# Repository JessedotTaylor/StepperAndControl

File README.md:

These are the complete development and handin files from one of my 4th year projects. 

The assignment brief is provided in the 'Context' subdirectory.
The first pass code for the AT-Mega 32u4 is in the 'Microcontroller Code' subdirectory.
The first pass QT UI code is in the 'PC Control Code' subdirectory.
The PCB design files are in the 'PCB Files' subdirectory. They were designed in Ki-Cad.

The final report, written between me and another student, Josh Baynes, is listed as 'Stepper and Control Report Jesse Taylor Josh Baynes'

In summary, we were asked to design a full mechatronic system for a 1-D stepper motor linear actuator, and write microcontroller and PC support software.
The microcontroller code is dependent on third party libraries, linked below.

TMC2130Stepper Library:
[[https://github.com/teemuatlut/TMC2130Stepper](https://github.com/teemuatlut/TMC2130Stepper)]

AccelStepper Library:
[[https://www.airspayce.com/mikem/arduino/AccelStepper/](https://www.airspayce.com/mikem/arduino/AccelStepper/)]

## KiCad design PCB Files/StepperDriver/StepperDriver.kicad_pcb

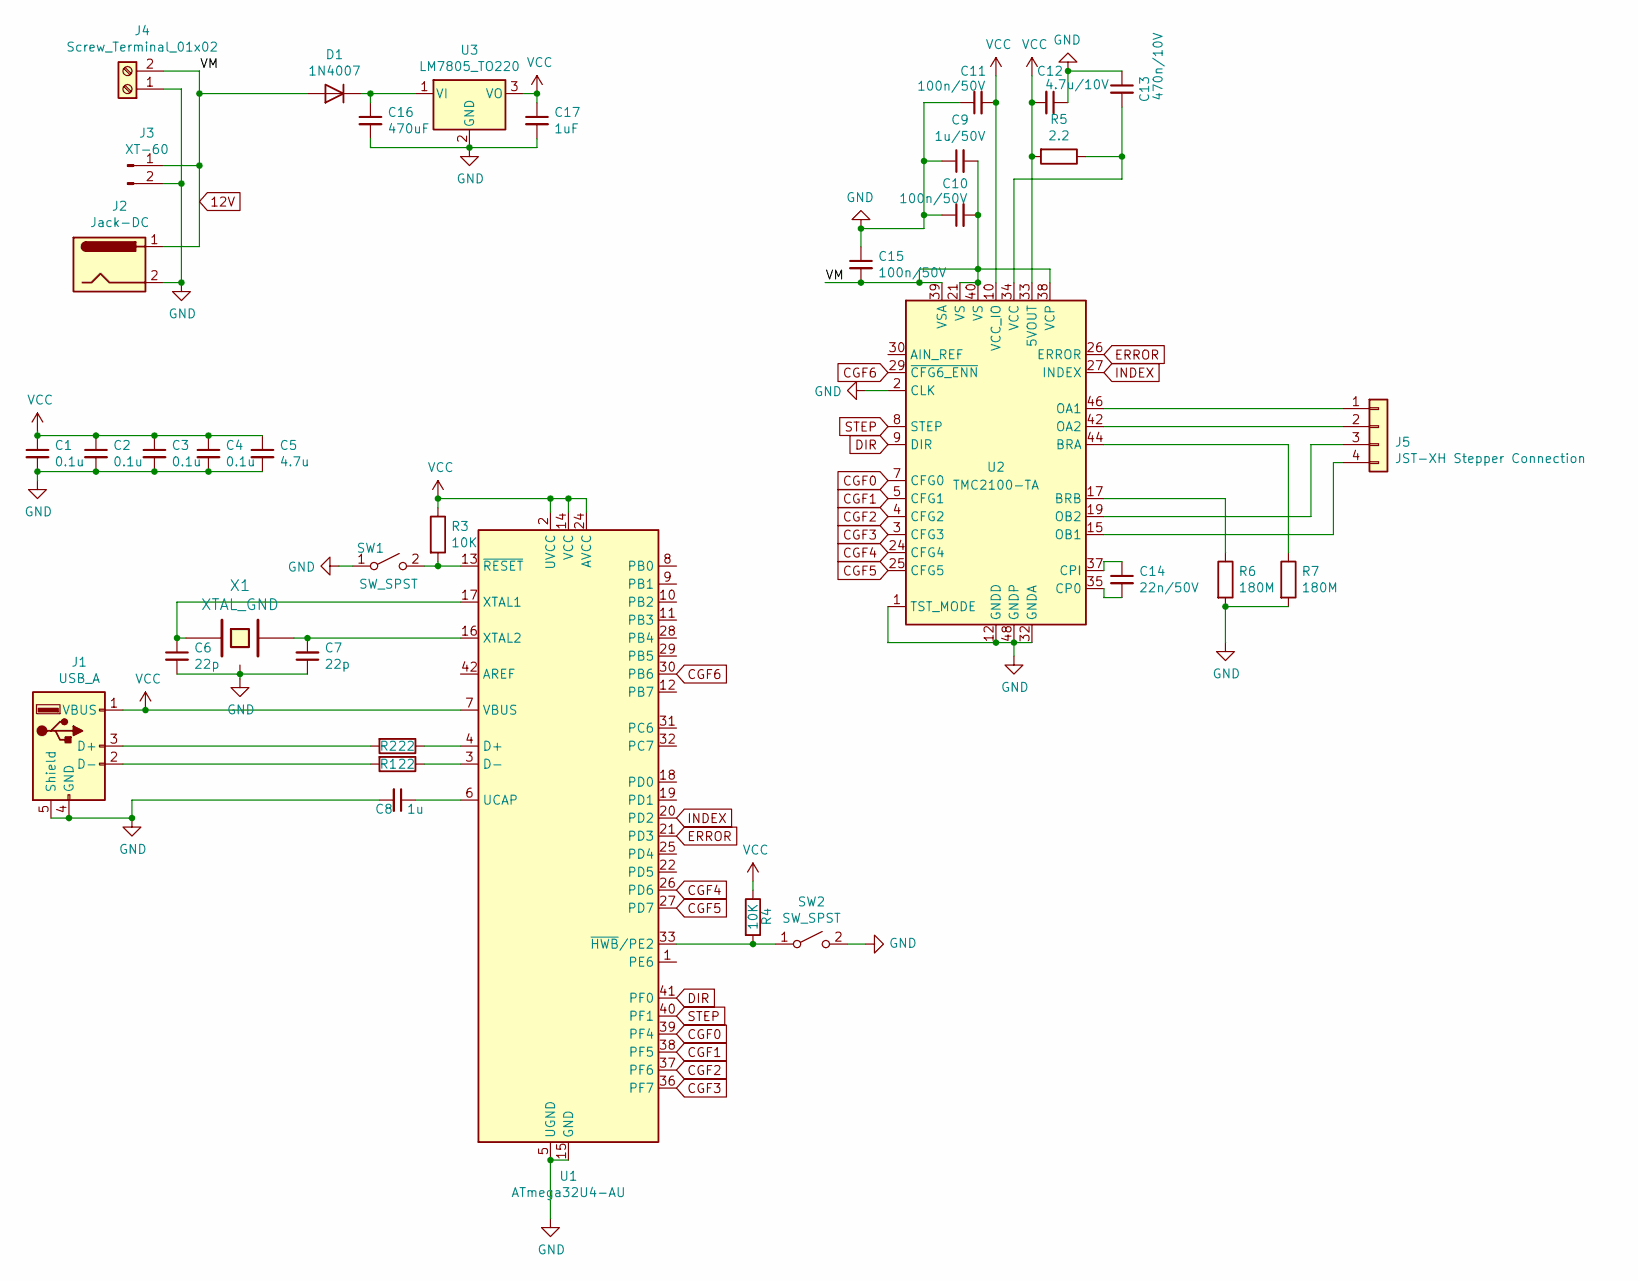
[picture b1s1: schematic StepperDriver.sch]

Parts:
C1, C2, C3, C4: 0.1u; C_0805_2012Metric_Pad1.15x1.40mm_HandSolder
C5: 4.7u; C_0805_2012Metric_Pad1.15x1.40mm_HandSolder
C6, C7: 22p; C_0805_2012Metric_Pad1.15x1.40mm_HandSolder
C8: 1u; C_0805_2012Metric_Pad1.15x1.40mm_HandSolder
C9: 1u/50V; C_0805_2012Metric_Pad1.15x1.40mm_HandSolder
C10, C11, C15: 100n/50V; C_2010_5025Metric_Pad1.52x2.65mm_HandSolder
C12: 4.7u/10V; C_0805_2012Metric_Pad1.15x1.40mm_HandSolder
C13: 470n/10V; C_0805_2012Metric_Pad1.15x1.40mm_HandSolder
C14: 22n/50V; C_2010_5025Metric_Pad1.52x2.65mm_HandSolder
C16: 470uF; CP_Radial_D4.0mm_P1.50mm
C17: 1uF; CP_Radial_D4.0mm_P1.50mm
D1: 1N4007; D_DO-41_SOD81_P10.16mm_Horizontal
J1: USB_A; USB_A_Molex_67643_Horizontal
J2: Jack-DC; BarrelJack_Horizontal
J3: XT-60; TestPoint_2Pads_Pitch5.08mm_Drill1.3mm
J4: Screw_Terminal_01x02; TerminalBlock_Altech_AK300-2_P5.00mm
J5: JST-XH Stepper Connection; JST_XH_B4B-XH-A_1x04_P2.50mm_Vertical
R1, R2: 22; R_0805_2012Metric_Pad1.15x1.40mm_HandSolder
R3, R4: 10K; R_0805_2012Metric_Pad1.15x1.40mm_HandSolder
R5: 2.2; R_0805_2012Metric_Pad1.15x1.40mm_HandSolder
R6, R7: 180M; R_0805_2012Metric_Pad1.15x1.40mm_HandSolder
SW1, SW2: SW_SPST; SW_SPST_TL3342
U1: ATmega32U4-AU; TQFP-44_10x10mm_P0.8mm
U2: TMC2100-TA; TQFP-48-1EP_7x7mm_P0.5mm_EP5x5mm_ThermalVias
U3: LM7805_TO220; TO-220-3_Vertical
X1: XTAL_GND; Crystal_SMD_SeikoEpson_FA238-4Pin_3.2x2.5mm_HandSoldering

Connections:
12V: C9.2, C10.2, C15.2, D1.2 (A), J2.1, J3.1, J4.2, U2.21 (VS), U2.38 (VCP), U2.39 (VSA), U2.40 (VS)
CGF0: U1.39 (PF4), U2.7 (CFG0)
CGF1: U1.38 (PF5), U2.5 (CFG1)
CGF2: U1.37 (PF6), U2.4 (CFG2)
CGF3: U1.36 (PF7), U2.3 (CFG3)
CGF4: U1.26 (PD6), U2.24 (CFG4)
CGF5: U1.27 (PD7), U2.25 (CFG5)
CGF6: U1.30 (PB6), U2.29 (~CFG6_ENN)
DIR: U1.41 (PF0), U2.9 (DIR)
ERROR: U1.21 (PD3), U2.26 (ERROR)
GND: C1.2, C2.2, C3.2, C4.2, C5.2, C6.2, C7.1, C8.2, C9.1, C10.1, C11.1, C12.1, C13.1, C15.1, C16.2, C17.2, J1.4 (GND), J1.5 (Shield), J2.2, J3.2, J4.1, R6.2, R7.2, SW1.1 (A), SW2.2 (B), U1.5 (UGND), U1.15 (GND), U1.23 (GND), U1.35 (GND), U1.43 (GND), U2.1 (TST_MODE), U2.2 (CLK), U2.6 (GNDD), U2.12 (GNDD), U2.13 (GNDP), U2.31 (GNDD), U2.32 (GNDA), U2.36 (GNDD), U2.48 (GNDP), U2.49 (GNDD), U3.2 (GND), X1.3
INDEX: U1.20 (PD2), U2.27 (INDEX)
unnamed: C6.1, U1.17 (XTAL1), X1.1
unnamed: C7.2, U1.16 (XTAL2), X1.2
unnamed: C8.1, U1.6 (UCAP)
unnamed: C13.2, R5.1, U2.34 (VCC)
unnamed: C14.1, U2.37 (CPI)
unnamed: C14.2, U2.35 (CP0)
unnamed: C16.1, D1.1 (K), U3.1 (VI)
unnamed: J1.2 (D-), R1.2
unnamed: J1.3 (D+), R2.2
unnamed: J5.1, U2.46 (OA1)
unnamed: J5.2, U2.42 (OA2)
unnamed: J5.3, U2.19 (OB2)
unnamed: J5.4, U2.15 (OB1)
unnamed: R1.1, U1.3 (D-)
unnamed: R2.1, U1.4 (D+)
unnamed: R3.2, SW1.2 (B), U1.13 (~RESET)
unnamed: R4.2, SW2.1 (A), U1.33 (~HWB~/PE2)
unnamed: R6.1, U2.17 (BRB)
unnamed: R7.1, U2.44 (BRA)
STEP: U1.40 (PF1), U2.8 (STEP)
VCC: C1.1, C2.1, C3.1, C4.1, C5.1, C11.2, C12.2, C17.1, J1.1 (VBUS), R3.1, R4.1, R5.2, U1.2 (UVCC), U1.7 (VBUS), U1.14 (VCC), U1.24 (AVCC), U1.34 (VCC), U1.44 (AVCC), U2.10 (VCC_IO), U2.33 (5VOUT), U3.3 (VO)

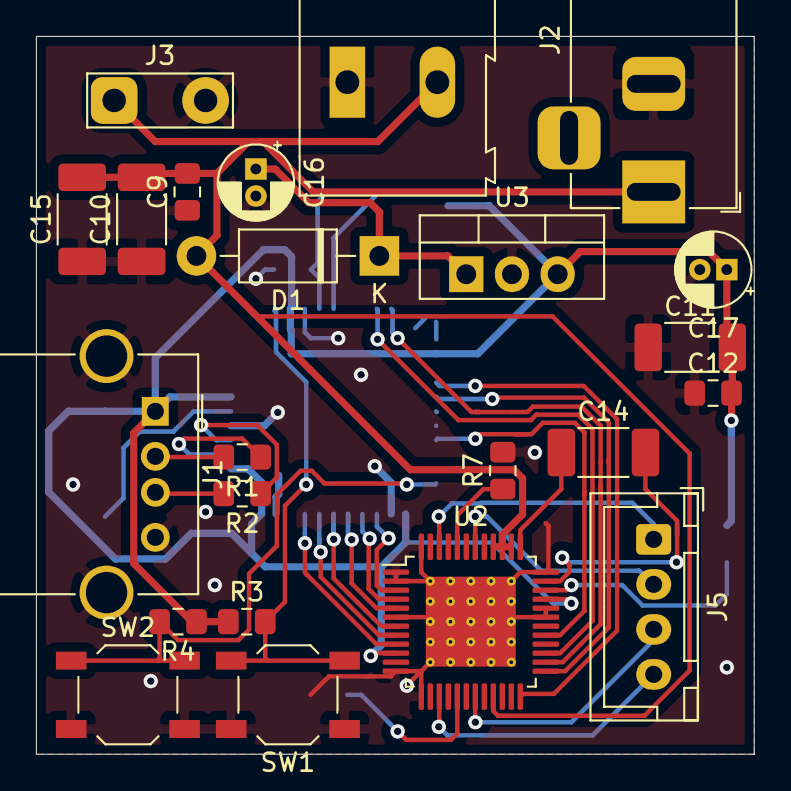
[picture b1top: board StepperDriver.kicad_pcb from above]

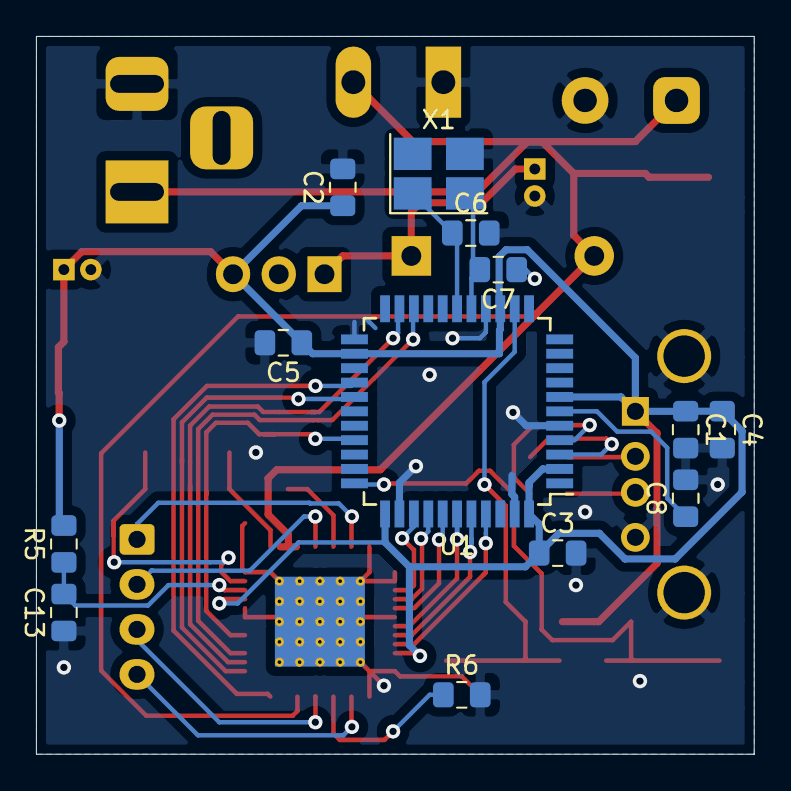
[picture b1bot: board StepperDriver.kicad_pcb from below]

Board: 2 copper layers, 39.9 x 39.9 mm, 36 parts (13 on the bottom side), 33 nets.

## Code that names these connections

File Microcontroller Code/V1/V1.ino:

#define ERROR_PIN 1 //PD3
#define INDEX_PIN 0 //PD2
#define EN_PIN 10 //PB6 CGF6
#define CS_PIN 14 //PF7 / A0
#define DIR_PIN 19 // PF0 / A5
#define STEP_PIN 18 //PF1 / A4
#define CGF0_PIN 17 //PF4 / A3
#define CGF1_PIN 16 //PF5 / A2
#define CGF2_PIN 15 //PF6 / A1
//#define CGF3_PIN 14 //PF7 / A0
#define CGF4_PIN 12 //PD6 
#define CGF5_PIN 6 // PD7


constexpr uint32_t steps_per_mm = 80;


#include <TMC2130Stepper.h>
#include <TMC2130Stepper_REGDEFS.h>
TMC2130Stepper driver = TMC2130Stepper(EN_PIN, DIR_PIN, STEP_PIN, CS_PIN);

#include <AccelStepper.h>
AccelStepper stepper = AccelStepper(stepper.DRIVER, STEP_PIN, DIR_PIN);

volatile byte error = false;
volatile int count = 0;
bool dir = false;

void pinError(void){
  error = true;
}

void index(void) {
  count++;
}


void setup() {
  // put your setup code here, to run once:
  pinMode(CGF0_PIN, OUTPUT);
  digitalWrite(CGF0_PIN, LOW); //Recommended setting for spreadcycle chopper
  pinMode(CGF4_PIN, OUTPUT);
  digitalWrite(CGF4_PIN, LOW); //Recommended setting for chopper hysteresis
  pinMode(CGF5_PIN, OUTPUT);
  digitalWrite(CGF5_PIN, HIGH); // Chopper blank time

  pinMode(ERROR_PIN, INPUT_PULLUP);   //These pins may trip on Serial Comms
  attachInterrupt(digitalPinToInterrupt(ERROR_PIN), pinError ,CHANGE);
  pinMode(INDEX_PIN, INPUT);
  attachInterrupt(digitalPinToInterrupt(INDEX_PIN), index ,CHANGE);

  Serial.begin(9600);
  while(!Serial); //Needed for 32u4 based boards
  Serial.println("Start...");
  SPI.begin();
  pinMode(MISO, INPUT_PULLUP);
  driver.begin();       // Initiate pins and registeries
  driver.rms_current(600);  // Set stepper current to 600mA. The command is the same as command TMC2130.setCurrent(600, 0.11, 0.5);
  driver.stealthChop(1);  // Enable extremely quiet stepping
  driver.sg_stall_value(0);
  
  digitalWrite(EN_PIN, HIGH); //LOW Enabled

  stepper.setMaxSpeed(50*steps_per_mm); // 100mm/s @ 80 steps/mm
  stepper.setAcceleration(1000*steps_per_mm); // 2000mm/s^2
  stepper.setEnablePin(EN_PIN);
  stepper.setPinsInverted(false, false, true);
  stepper.enableOutputs();

    // Set stepper interrupt
  {
    cli();//stop interrupts
    TCCR1A = 0;// set entire TCCR1A register to 0
    TCCR1B = 0;// same for TCCR1B
    TCNT1  = 0;//initialize counter value to 0
    OCR1A = 256;// = (16*10^6) / (1*1024) - 1 (must be <65536)
    // turn on CTC mode
    TCCR1B |= (1 << WGM12);
    // Set CS11 bits for 8 prescaler
    TCCR1B |= (1 << CS11);// | (1 << CS10);  
    // enable timer compare interrupt
    TIMSK1 |= (1 << OCIE1A);
    sei();//allow interrupts
  }
  bool dir = false;

}

ISR(TIMER1_COMPA_vect){
  PORTF |= 1 << 0;
  PORTF &= ~(1 << 0);
}

void loop() {
  static uint32_t last_time = 0;
  uint32_t ms = millis();
  // put your main code here, to run repeatedly:
  if((ms-last_time) > 500) { //run every 0.5s
    while(!Serial.available());
    char inc[80];
    int i = 0;
    while(Serial.available() > 0) {
      inc[i++] = Serial.read();
    }
    inc[i] = '\0';
    int n;
    switch (inc[0]){
       case 'O': // Toggle Enable
       {
          digitalWrite(EN_PIN, !digitalRead(EN_PIN));
          break;
       }
       case 'D': //Toggle Direction
       {
          dir = !dir;
          driver.shaft_dir(dir);
          break;
       }
      case 'F': //Fullstep X steps
      {
          sscanf(inc+1, "%d", &n); 
          count = 0;
          digitalWrite(EN_PIN, LOW);  //Active LOW
          while (count < n) {};     //Very bad programming
          digitalWrite(EN_PIN, HIGH); // Active LOW
          break;
      }
      case 'M': //Set microsteps
      {
          sscanf(inc+1, "%d", &n); 
          driver.microsteps(n);
          break;
      }
      case 'X': // goto x.y absolute position
          break;
  
      case 'Z': // goto x.y relative position
          break;
  
      case 'H': // reHome
          driver.shaft_dir(0);
          static uint32_t last_time = 0;
          uint32_t ms = millis();
          
          if((ms-last_time) > 10) //run every 0.01s
          {
            last_time = ms;
            uint32_t drv_status = driver.DRV_STATUS();
            while ((drv_status & SG_RESULT_bm)>>SG_RESULT_bp != 0) {};  //Again with the bad programming
          }
          driver.shaft_dir(dir);
          break;
  
      case 'S':
          switch (inc[2]) {
            case 'M':
            {
              sscanf(inc+3, "%d", &n);
              stepper.setMaxSpeed(n * steps_per_mm);
              break;
            }
            case 'A':
            {
              sscanf(inc+3, "%d", &n);
              stepper.setAcceleration(n * steps_per_mm);
              break;
            }  
            case 'S':
            {
              sscanf(inc+3, "%d", &n);
              driver.sg_stall_value(n);
              break;
            } 
            default:
              break;
          }
          
      default:
         break;
    }
  }

  if (error) {  // Error Pin goes high
    error = false;
    Serial.println("E");
    digitalWrite(EN_PIN, LOW);
  }
  
  
  if((ms-last_time) > 100) //run every 0.1s
  {
    last_time = ms;
    uint32_t drv_status = driver.DRV_STATUS();
    if ((drv_status & SG_RESULT_bm)>>SG_RESULT_bp == 0){ // Driver stalled
      Serial.println("N");
      digitalWrite(EN_PIN, LOW);
    }
  }


}
